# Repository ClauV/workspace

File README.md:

# workspace
kikad,proteus ant atmel studio

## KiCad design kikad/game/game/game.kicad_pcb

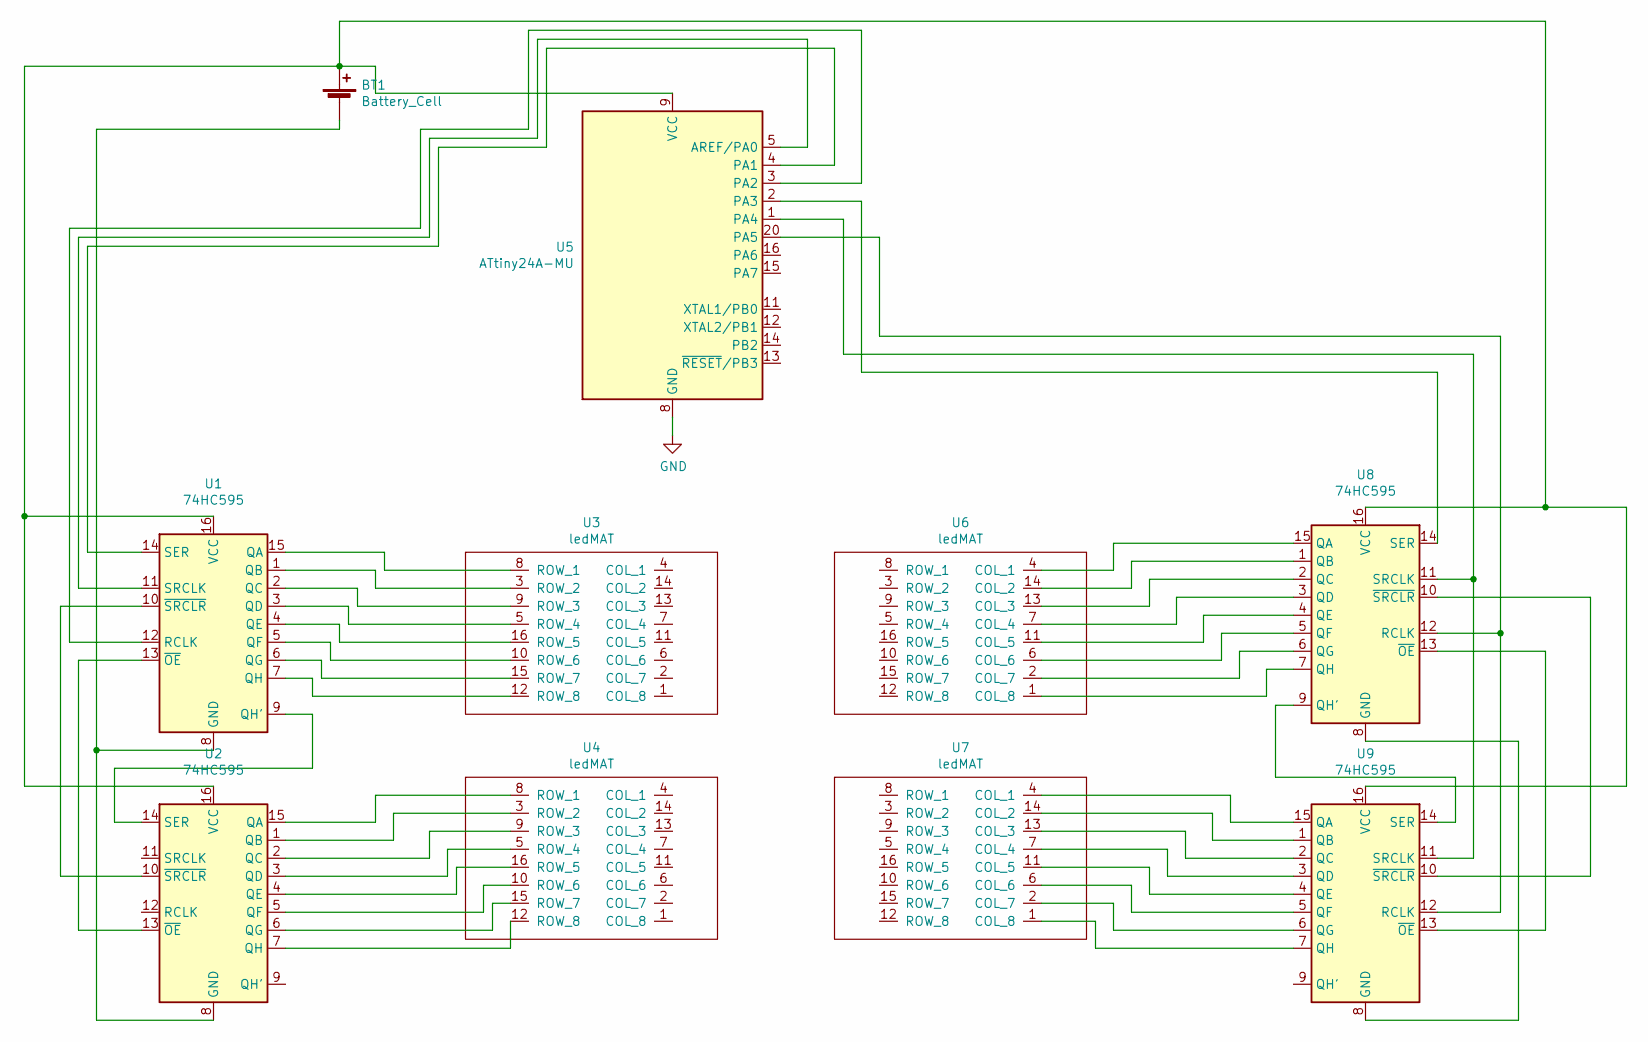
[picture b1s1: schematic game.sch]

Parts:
BT1: Battery_Cell; BatteryHolder_Keystone_3034_1x20mm
U1, U2, U8, U9: 74HC595; DIP-16_W7.62mm
U3, U4, U6, U7: ledMAT; Game
U5: ATtiny24A-MU; QFN-20-1EP_4x4mm_P0.5mm_EP2.6x2.6mm

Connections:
GND: U5.8 (GND), U5.21 (GND)
unnamed: BT1.1 (+), U1.16 (VCC), U2.16 (VCC), U5.9 (VCC), U8.16 (VCC), U9.16 (VCC)
unnamed: BT1.2 (-), U1.8 (GND), U2.8 (GND)
unnamed: U1.1 (QB), U3.3 (ROW_2)
unnamed: U1.2 (QC), U3.9 (ROW_3)
unnamed: U1.3 (QD), U3.5 (ROW_4)
unnamed: U1.4 (QE), U3.16 (ROW_5)
unnamed: U1.5 (QF), U3.10 (ROW_6)
unnamed: U1.6 (QG), U3.15 (ROW_7)
unnamed: U1.7 (QH), U3.12 (ROW_8)
unnamed: U1.9 (QH'), U2.14 (SER)
unnamed: U1.10 (~SRCLR), U2.10 (~SRCLR)
unnamed: U1.11 (SRCLK), U5.5 (AREF/PA0)
unnamed: U1.12 (RCLK), U5.3 (PA2)
unnamed: U1.13 (~OE), U2.13 (~OE)
unnamed: U1.14 (SER), U5.4 (PA1)
unnamed: U1.15 (QA), U3.8 (ROW_1)
unnamed: U2.1 (QB), U4.3 (ROW_2)
unnamed: U2.2 (QC), U4.9 (ROW_3)
unnamed: U2.3 (QD), U4.5 (ROW_4)
unnamed: U2.4 (QE), U4.16 (ROW_5)
unnamed: U2.5 (QF), U4.10 (ROW_6)
unnamed: U2.6 (QG), U4.15 (ROW_7)
unnamed: U2.7 (QH), U4.12 (ROW_8)
unnamed: U2.15 (QA), U4.8 (ROW_1)
unnamed: U5.1 (PA4), U8.11 (SRCLK), U9.11 (SRCLK)
unnamed: U5.2 (PA3), U8.14 (SER)
unnamed: U5.20 (PA5), U8.12 (RCLK), U9.12 (RCLK)
unnamed: U6.1 (COL_8), U8.7 (QH)
unnamed: U6.2 (COL_7), U8.6 (QG)
unnamed: U6.4 (COL_1), U8.15 (QA)
unnamed: U6.6 (COL_6), U8.5 (QF)
unnamed: U6.7 (COL_4), U8.3 (QD)
unnamed: U6.11 (COL_5), U8.4 (QE)
unnamed: U6.13 (COL_3), U8.2 (QC)
unnamed: U6.14 (COL_2), U8.1 (QB)
unnamed: U7.1 (COL_8), U9.7 (QH)
unnamed: U7.2 (COL_7), U9.6 (QG)
unnamed: U7.4 (COL_1), U9.15 (QA)
unnamed: U7.6 (COL_6), U9.5 (QF)
unnamed: U7.7 (COL_4), U9.3 (QD)
unnamed: U7.11 (COL_5), U9.4 (QE)
unnamed: U7.13 (COL_3), U9.2 (QC)
unnamed: U7.14 (COL_2), U9.1 (QB)
unnamed: U8.8 (GND), U9.8 (GND)
unnamed: U8.9 (QH'), U9.14 (SER)
unnamed: U8.10 (~SRCLR), U9.10 (~SRCLR)
unnamed: U8.13 (~OE), U9.13 (~OE)

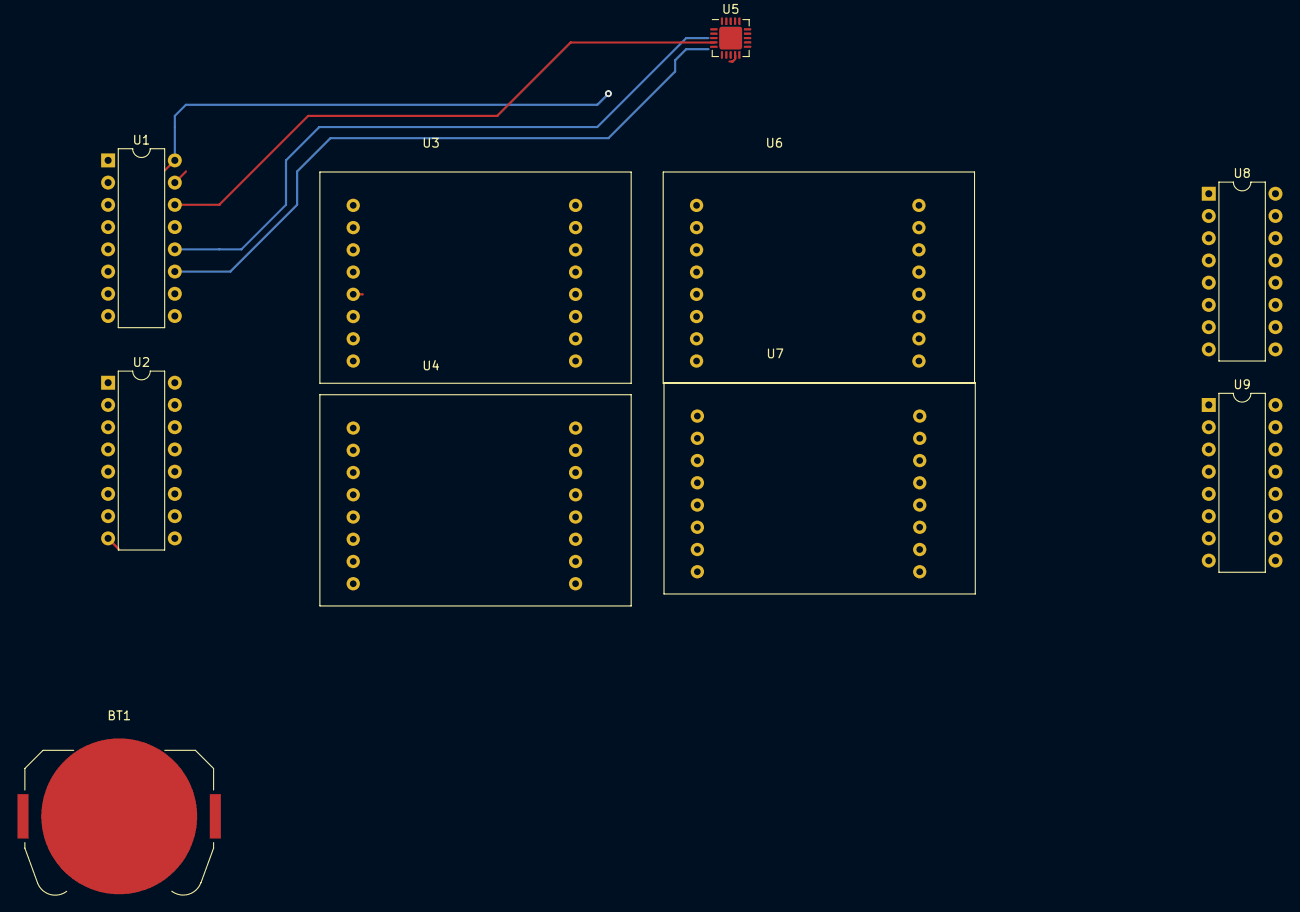
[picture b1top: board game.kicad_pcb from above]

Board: 2 copper layers, 10 parts (0 on the bottom side), 48 nets.

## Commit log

2019-12-16 line blink
2019-12-16 proteus file
2019-12-16 working library
2019-12-18 readme
2019-12-28 shift lib initial
2019-12-28 shift bug fix
2019-12-31 game
2020-01-19 printf proiect
